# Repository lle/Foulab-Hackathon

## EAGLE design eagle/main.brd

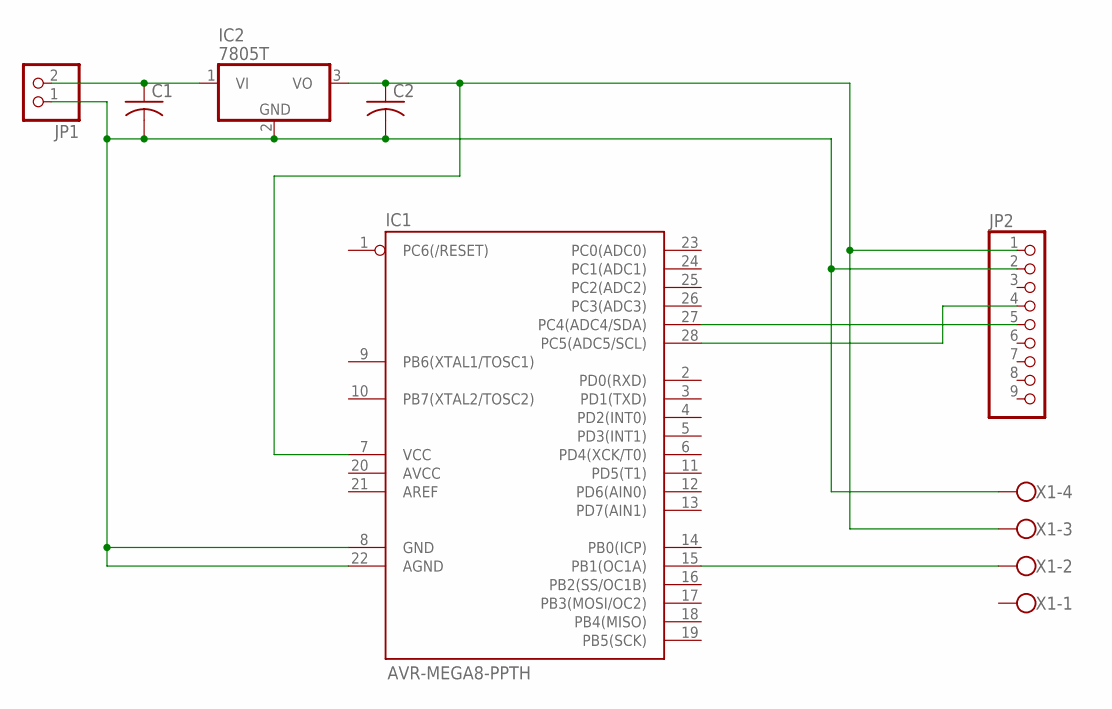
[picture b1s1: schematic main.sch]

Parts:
C1: C-US050-075X075; C050-075X075
C2: C-US025-050X050; C025-050X050
IC1: AVR-MEGA8-PPTH; DIL28-3
IC2: 7805T; TO220H
JP1: PINHD-1X2; 1X02
JP2: PINHD-1X9; 1X09
X1: W237-4

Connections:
unnamed: C1.1, IC2.1 (VI), JP1.2
unnamed: C1.2, C2.2, IC1.8 (GND), IC1.22 (AGND), IC2.2 (GND), JP1.1, JP2.2, X1.4
unnamed: C2.1, IC1.7 (VCC), IC2.3 (VO), JP2.1, X1.3
unnamed: IC1.28 (PC5(ADC5/SCL)), JP2.4
unnamed: IC1.27 (PC4(ADC4/SDA)), JP2.5
unnamed: IC1.15 (PB1(OC1A)), X1.2

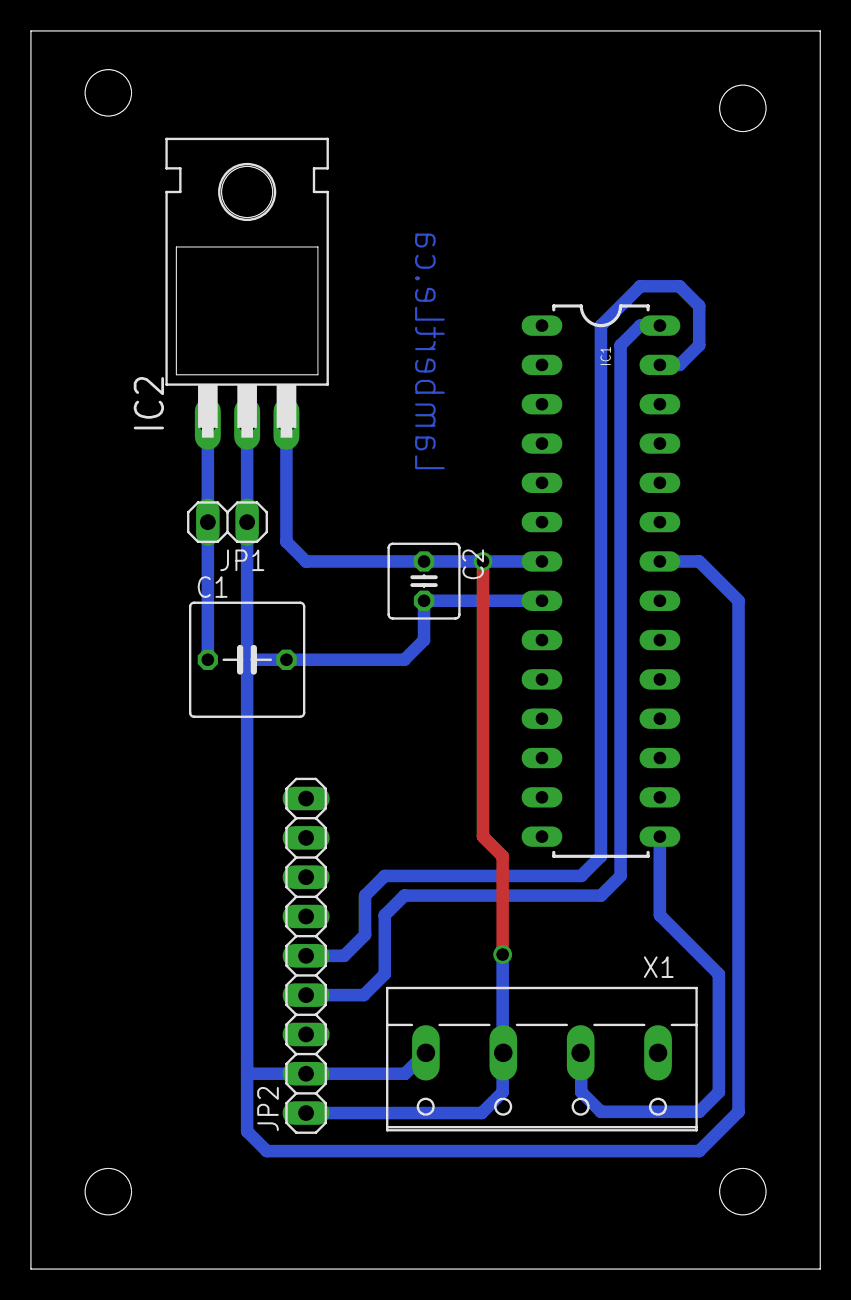
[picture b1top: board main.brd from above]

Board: 2 copper layers, 51.0 x 80.0 mm, 7 parts (0 on the bottom side), 6 nets.

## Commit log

2013-08-11 upload full code
2013-08-11 added eagle files
2013-08-11 Added license

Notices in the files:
parts and their libraries:
SparkFun: Licensing: CC v3.0 Share-Alike You are welcome to use this library for commercial purposes.
